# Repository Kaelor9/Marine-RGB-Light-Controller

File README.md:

<h1 align="center">Marine RGB Light Controller</h1>

<p align="center">
  Professional ESP32-S3 controller for addressable RGB LED installations in marine, automotive and industrial environments.
</p>

<p align="center">
  
</p>

---

## About

The **Marine RGB Light Controller** is a custom-designed ESP32-S3 controller developed for reliable operation in demanding electrical environments.

Unlike generic ESP32 development boards, it integrates protected power electronics, optically isolated inputs, dual level-shifted LED outputs and dedicated expansion interfaces into a single compact PCB.

Originally designed for marine lighting systems, the controller is equally suited for automotive, off-road, RV, architectural and industrial LED installations.

---

## Why this controller?

Most ESP32 development boards are intended for prototyping and require additional external circuitry before they are suitable for real-world installations.

The Marine RGB Light Controller integrates the essential hardware needed for reliable field deployment:

- Protected 12–24V power input
- Reverse polarity protection
- TVS surge suppression
- Optically isolated inputs
- Dual 5V LED data outputs
- USB-C programming
- GPIO & I²C expansion
- Compact installation-ready PCB

This significantly reduces external wiring while improving robustness and long-term reliability.

---

## Key Features

- ⚡ Protected 12–24V DC controller input
- 🔋 Direct VIN pass-through LED power output
- 🌈 Two independent 5V level-shifted LED data outputs
- 🔒 Two high-speed optically isolated digital inputs
- 📡 Wi-Fi & Bluetooth LE
- 🔌 USB-C programming
- 🔧 GPIO & I²C expansion
- 🛡 TVS, fuse and reverse polarity protection
- ⚓ Designed for harsh electrical environments

---

## Applications

The controller is suitable for a wide range of professional LED installations, including:

- ⚓ Marine lighting
- 🚙 Automotive lighting
- 🏕 Camper & RV installations
- 🏭 Industrial automation
- 🏡 Architectural lighting
- 💡 Custom RGB LED projects

---

## Hardware

The PCB integrates everything required for a professional LED controller:

- ESP32-S3-WROOM-1-N8R8
- High-efficiency buck converter
- Low-noise 3.3V LDO
- USB-C programming interface
- Dual 5V level shifters
- High-speed optocouplers
- Protected controller power supply
- GPIO & I²C expansion
- Dedicated LED power distribution

---

## Technical Specifications

| Feature | Specification |
|---------|---------------|
| MCU | ESP32-S3-WROOM-1-N8R8 |
| Flash | 8 MB |
| PSRAM | 8 MB |
| Input Voltage | 12–24V DC |
| Controller Protection | Fuse + Reverse Polarity + TVS |
| LED Supply | Direct VIN Pass-through |
| LED Outputs | 2 × 5V Logic (Level Shifted) |
| Digital Inputs | 2 × Optically Isolated |
| Wireless | Wi-Fi 2.4 GHz + Bluetooth LE |
| USB | USB-C |
| Expansion | GPIO + I²C |

---

## Pinout

| Connection | Function |
|------------|----------|
| VIN | 12–24V DC Input |
| AUX Power | Direct VIN Pass-through |
| DATA 1 | 5V LED Data Output |
| DATA 2 | 5V LED Data Output |
| ISO IN1 | Optically Isolated Input |
| ISO IN2 | Optically Isolated Input |
| SDA / SCL | I²C Expansion |
| IO8 / IO9 | GPIO Expansion |
| IO10 / IO11 | GPIO Expansion |
| 3V3 | 3.3V Output |
| 5V | 5V Output |
| GND | Ground |

---

## Gallery

---

## Software

The firmware is developed for the ESP32-S3 using the Arduino framework and is designed around a modern, responsive web interface.

Configuration is performed directly from any web browser without requiring additional software. The modular firmware architecture allows new LED effects and features to be added easily.

Current and planned features include:

- Modern Web UI
- RGB Color Picker
- Brightness Control
- LED Effects
- Wi-Fi Configuration
- mDNS Support
- OTA Firmware Updates
- FastLED Support
- Configuration Storage

---

## Repository Structure

```text
.
├── docs/
│   ├── images/
│   ├── hardware.md
│   ├── software.md
│   └── fabrication.md
│
├── firmware/
│   └── Marine_RGB_Controller/
│
├── hardware/
│   ├── kicad/
│   ├── fabrication/
│   └── 3d/
│
├── site/
│
├── LICENSE
└── README.md
```

---

## Documentation

Project documentation is located inside the **docs** directory.

Available documentation includes:

- Hardware Design
- Power Supply
- LED Outputs
- Optically Isolated Inputs
- Pinout
- Firmware
- Fabrication
- Getting Started

---

## Important Information

> [!IMPORTANT]
>
> The **LED power output is a direct pass-through of the input supply voltage.**
>
> - LED VOUT = VIN
> - The LED supply is **not reverse polarity protected**
> - The LED supply is **not fused**
> - Only the controller electronics are protected by the onboard fuse, TVS diode and reverse polarity protection
> - External protection should be added where required by the installation

---

## Project Status

| Hardware | Firmware | Documentation |
|----------|----------|---------------|
| ✅ Revision 1 Complete | 🚧 In Development | 🚧 In Progress |

---

## Roadmap

### Hardware

- [x] Hardware Revision 1
- [x] Protected Power Supply
- [x] USB-C Programming
- [x] Dual LED Outputs
- [x] Optically Isolated Inputs

### Firmware

- [ ] Complete Web Interface
- [ ] OTA Updates
- [ ] MQTT Support
- [ ] Home Assistant Integration
- [ ] Additional LED Effects
- [ ] Configuration Backup & Restore

---

## License

This project is proprietary.

Copyright © 2026 Anders Merrild

All rights reserved.

No permission is granted to copy, modify, distribute, manufacture, publish, sublicense or use any part of this project without prior written permission from the copyright holder.

See the [LICENSE](LICENSE) file for full terms.

---

<p align="center">

Designed and developed by <strong>Kaelor9</strong>

<br>

ESP32 • Marine Electronics • Professional RGB Lighting Controller

</p>

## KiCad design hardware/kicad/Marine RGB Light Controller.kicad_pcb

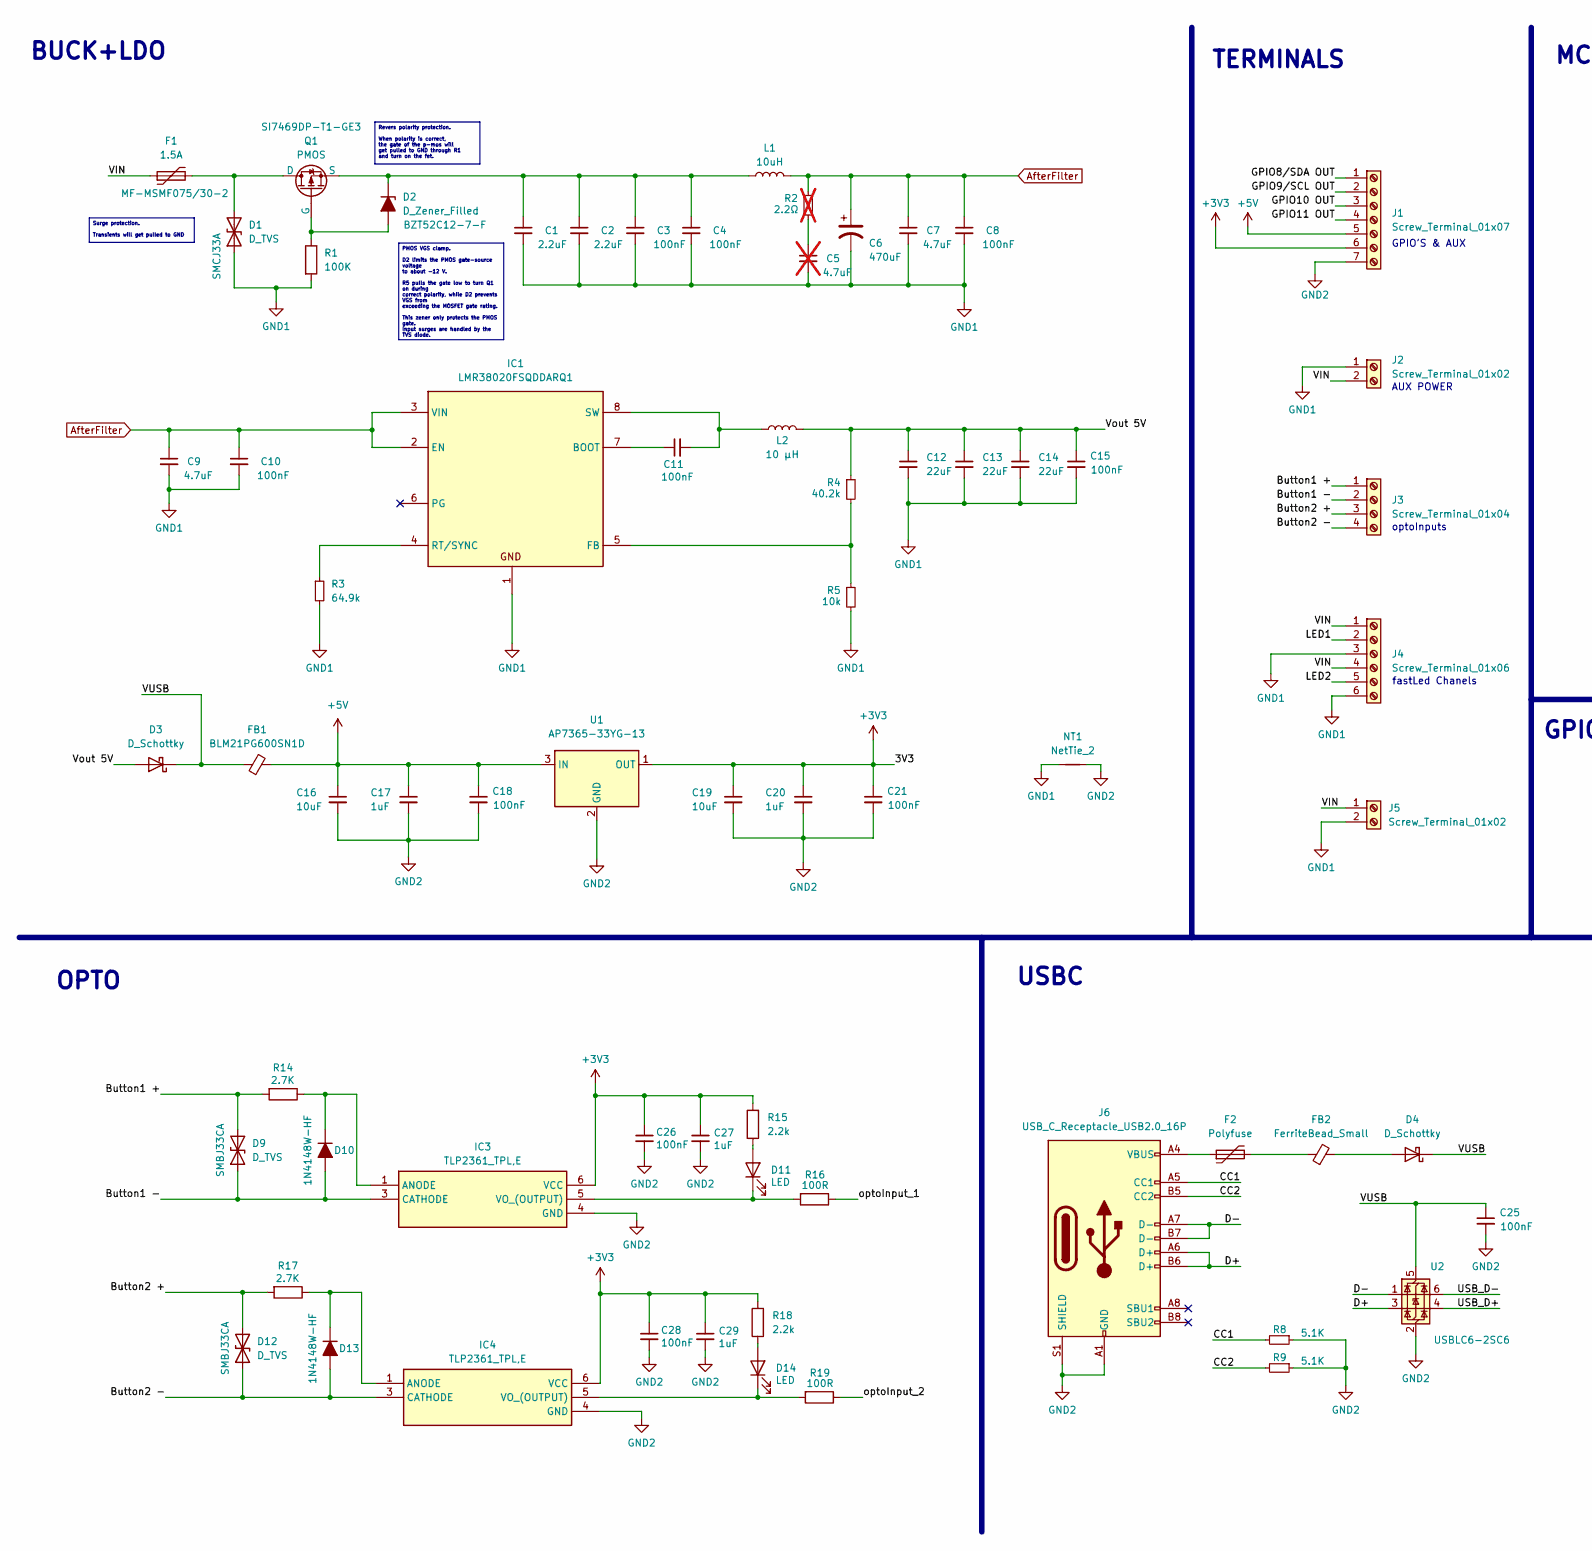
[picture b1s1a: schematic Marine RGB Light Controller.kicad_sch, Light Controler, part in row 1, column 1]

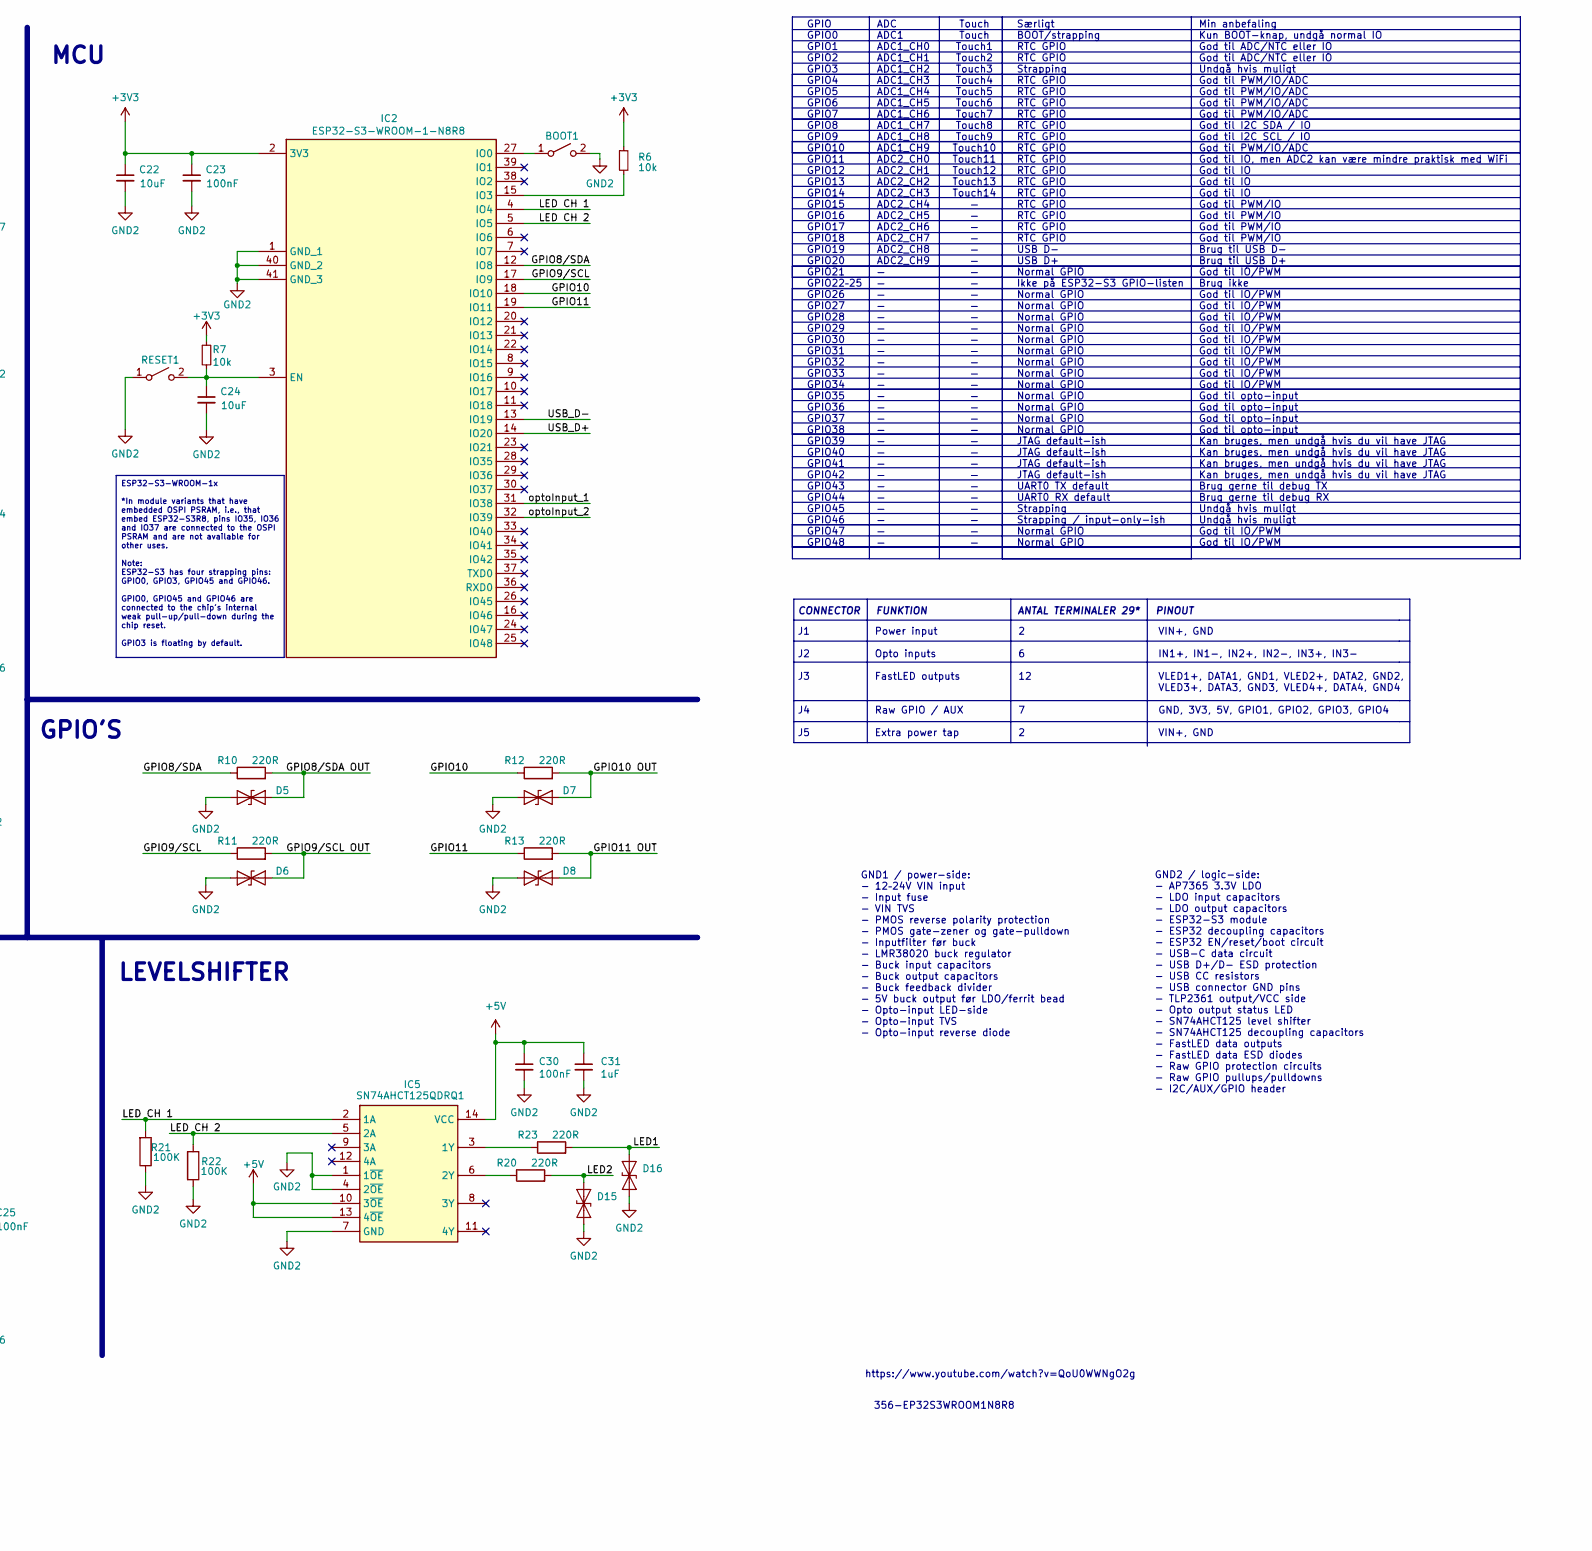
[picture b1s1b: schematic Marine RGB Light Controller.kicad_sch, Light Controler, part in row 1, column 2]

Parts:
BOOT1: SW [PTS810SJM250SMTRLFS]
C1, C2: 2.2uF; C_1206_3216Metric; Voltage Rating VDC 100V
C3, C4, C8, C10: 100nF; C_0603_1608Metric; Voltage Rating VDC 100V
C5: 4.7uF; C_1206_3216Metric; Voltage Rating VDC 100V; not fitted
C6: 470uF; CP_Radial_D12.5mm_P5.00mm; Voltage Rating VDC 63V
C7, C9: 4.7uF; C_1206_3216Metric; Voltage Rating VDC 100V
C11, C15, C18, C21, C23, C25, C26, C28, C30: 100nF; C_0603_1608Metric; Voltage Rating VDC 50V
C12, C13, C14: 22uF; C_1206_3216Metric; Voltage Rating VDC 16V
C16, C19: 10uF; C_1206_3216Metric; Voltage Rating VDC 16V
C17, C20: 1uF; C_0805_2012Metric; Voltage Rating VDC 25V
C22, C24: 10uF; C_0603_1608Metric; Voltage Rating VDC 35V
C27, C29, C31: 1uF; C_0805_2012Metric; Voltage Rating VDC 50V
D1: D_TVS; D_SMC
D2: D_Zener_Filled; D_SOD-123
D3, D4: D_Schottky; D_SOD-123
D5, D6, D7, D8, D15, D16: SD05_SOD323; D_SOD-323
D9, D12: D_TVS; D_SMB
D10, D13: D_SOD-123
D11, D14: LED; LED_0603_1608Metric
F1: 1.5A; Fuse_1812_4532Metric; Voltage Rating VDC 30 VDC
F2: Polyfuse; Fuse_1206_3216Metric
FB1: BLM21PG600SN1D; R_0805_2012Metric
FB2: FerriteBead_Small; R_0805_2012Metric
IC1: LMR38020FSQDDARQ1; Texas_R-PDSO-G8_EP2.95x4.9mm_Mask2.4x3.1mm; Voltage Rating VDC 80V
IC2: ESP32-S3-WROOM-1-N8R8; ESP32S3WROOM1N8R8; Mouser Part Number 356-EP32S3WROOM1N8R8
IC3, IC4: TLP2361_TPL,E; SOIC-6; Mouser Part Number 757-TLP2361(TPLE
IC5: SN74AHCT125QDRQ1; SOIC-14_3.9x8.7mm_P1.27mm; Mouser Part Number 595-SN74AHCT125QDRQ1
J1: Screw_Terminal_01x07; Fixed Terminal Blocks 7P 3.5mm 90DEG
J2: Screw_Terminal_01x02; Fixed Terminal Blocks 2P 3.5mm 0DEG
J3: Screw_Terminal_01x04; Fixed Terminal Blocks 4P 3.5mm 90DEG
J4: Screw_Terminal_01x06; Fixed Terminal Blocks 6P 3.5mm 90DEG
J5: Screw_Terminal_01x02; 2_Position Screw Terminal 5mm Pitch
J6: USB_C_Receptacle_USB2.0_16P; USB C [USB494000A]
L1: 10uH; L_Bourns_SRP1038C_10.0x10.0mm
L2: 10 µH; L_12x12mm_H6mm
NT1: NetTie_2; NetTie-2_SMD_Pad0.5mm
Q1: PMOS; P-MOS [SI7141DPT1GE3]; Voltage Rating VDC 80V
R1, R21, R22: 100K; R_0603_1608Metric
R2: 2.2Ω; R_1206_3216Metric; Voltage Rating VDC 200V; not fitted
R3: 64.9k; R_0603_1608Metric; Voltage Rating VDC 150 V
R4: 40.2k; R_0603_1608Metric; Voltage Rating VDC 150V
R5, R6, R7: 10k; R_0603_1608Metric
R8, R9: 5.1K; R_0603_1608Metric; Voltage Rating VDC 150V
R10, R11, R12, R13, R20, R23: 220R; R_0805_2012Metric; Voltage Rating VDC 150V
R14, R17: 2.7K; R_1206_3216Metric
R15, R18: 2.2k; R_0603_1608Metric
R16, R19: 100R; R_0603_1608Metric
RESET1: SW [PTS810SJM250SMTRLFS]
U1: AP7365-33YG-13; SOT-89-3
U2: USBLC6-2SC6; SOT-23-6

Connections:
+3V3: C19.1, C20.1, C21.1, C22.1, C23.1, C26.1, C27.1, C28.1, C29.1, IC2.2 (3V3), IC3.6 (VCC), IC4.6 (VCC), J1.6, R6.1, R7.1, R15.2, R18.2, U1.1 (OUT)
+5V: C16.1, C17.1, C18.1, C30.1, C31.1, FB1.2, IC5.10 (3~OE), IC5.13 (4~OE), IC5.14 (VCC), J1.5, U1.3 (IN)
/Button1 +: D9.2 (A2), J3.1, R14.2
/Button1 -: D9.1 (A1), D10.2 (A), IC3.3 (CATHODE), J3.2
/Button2 +: D12.2 (A2), J3.3, R17.2
/Button2 -: D12.1 (A1), D13.2 (A), IC4.3 (CATHODE), J3.4
/CC1: J6.A5 (CC1), R8.2
/CC2: J6.B5 (CC2), R9.2
/D+: J6.A6 (D+), J6.B6 (D+), U2.3 (I/O2)
/D-: J6.A7 (D-), J6.B7 (D-), U2.1 (I/O1)
/GPIO8/SDA: IC2.12 (IO8), R10.1
/GPIO8/SDA OUT: D5.2 (A2), J1.1, R10.2
/GPIO9/SCL: IC2.17 (IO9), R11.1
/GPIO9/SCL OUT: D6.2 (A2), J1.2, R11.2
/GPIO10: IC2.18 (IO10), R12.1
/GPIO10 OUT: D7.2 (A2), J1.3, R12.2
/GPIO11: IC2.19 (IO11), R13.1
/GPIO11 OUT: D8.2 (A2), J1.4, R13.2
/LED1: D16.2 (A2), J4.2, R23.2
/LED2: D15.2 (A2), J4.5, R20.2
/LED CH 1: IC2.4 (IO4), IC5.2 (1A), R21.2
/LED CH 2: IC2.5 (IO5), IC5.5 (2A), R22.2
/USB_D+: IC2.14 (IO20), U2.4 (I/O2)
/USB_D-: IC2.13 (IO19), U2.6 (I/O1)
/VIN: F1.1, J2.2, J4.1, J4.4, J5.1
/VUSB: C25.1, D3.1 (K), D4.1 (K), FB1.1, U2.5 (VBUS)
/Vout 5V: C12.1, C13.1, C14.1, C15.1, D3.2 (A), L2.2, R4.1
/optoInput_1: IC2.31 (IO38), R16.1
/optoInput_2: IC2.32 (IO39), R19.1
AfterFilter: C6.1, C7.1, C8.1, C9.1, C10.1, IC1.2 (EN), IC1.3 (VIN), L1.2, R2.1
GND1: C1.2, C2.2, C3.2, C4.2, C5.2, C6.2, C7.2, C8.2, C9.2, C10.2, C12.2, C13.2, C14.2, C15.2, D1.1 (A1), IC1.1, IC1.9 (EP), J2.1, J4.3, J4.6, J5.2, NT1.1, R1.2, R3.2, R5.2; also elsewhere on the board
GND2: BOOT1.2 (B), C16.2, C17.2, C18.2, C19.2, C20.2, C21.2, C22.2, C23.2, C24.2, C25.2, C26.2, C27.2, C28.2, C29.2, C30.2, C31.2, D5.1 (A1), D6.1 (A1), D7.1 (A1), D8.1 (A1), D15.1 (A1), D16.1 (A1), IC2.1 (GND_1), IC2.40 (GND_2), IC2.41 (GND_3), IC2.42 (GND_4), IC2.43 (GND_5), IC2.44 (GND_6), IC2.45 (GND_7), IC2.46 (GND_8), IC2.47 (GND_9), IC2.48 (GND_10), IC2.49 (GND_11), IC3.4 (GND), IC4.4 (GND), IC5.1 (1~OE), IC5.4 (2~OE), IC5.7 (GND), J1.7, J6.A1 (GND), J6.A12 (GND), J6.B1 (GND), J6.B12 (GND), J6.S1 (SHIELD), NT1.2, R8.1, R9.1, R21.1, R22.1, RESET1.1 (A), U1.2 (GND), U2.2 (GND); also elsewhere on the board
unnamed 32: BOOT1.1 (A), IC2.27 (IO0); also elsewhere on the board
unnamed: C5.1, R2.2
unnamed: D1.2 (A2), F1.2, Q1.3 (D)
unnamed: D2.2 (A), Q1.2 (G), R1.1
unnamed: C1.1, C2.1, C3.1, C4.1, D2.1 (K), L1.1, Q1.1 (S)
unnamed: D4.2 (A), FB2.2
unnamed: D10.1 (K), IC3.1 (ANODE), R14.1
unnamed: D11.2 (A), R15.1
unnamed: D11.1 (K), IC3.5 (VO_(OUTPUT)), R16.2
unnamed: D13.1 (K), IC4.1 (ANODE), R17.1
unnamed: D14.2 (A), R18.1
unnamed: D14.1 (K), IC4.5 (VO_(OUTPUT)), R19.2
unnamed: F2.1, J6.A4 (VBUS), J6.A9 (VBUS), J6.B4 (VBUS), J6.B9 (VBUS)
unnamed: F2.2, FB2.1
unnamed: C11.1, IC1.7 (BOOT)
unnamed: IC1.5 (FB), R4.2, R5.1
unnamed: IC1.4 (RT/SYNC), R3.1
unnamed: C11.2, IC1.8 (SW), L2.1
unnamed 50: C24.1, IC2.3 (EN), R7.2, RESET1.2 (B); also elsewhere on the board
unnamed: IC2.15 (IO3), R6.2
unnamed: IC5.3 (1Y), R23.1
unnamed: IC5.6 (2Y), R20.1

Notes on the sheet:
ESP32-S3-WROOM-1x *In module variants that have embedded OSPI PSRAM, i.e., that embed ESP32-S3R8, pins IO35, IO36 and IO37 are connected to the OSPI PSRAM and are not available for other uses. Note: ESP32-S3 has four strapping pins: GPIO0, GPIO3, GPIO45 and GPIO46. GPIO0, GPIO45 and GPIO46 are conn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
PMOS VGS clamp. D2 limits the PMOS gate-source voltage to about -12 V. R5 pulls the gate low to turn Q1 on during correct polarity, while D2 prevents VGS from exceeding the MOSFET gate rating. This zener only protects the PMOS gate. Input surges are handled by the TVS diode.
Surge protection. Transients will get pulled to GND
Revers polarity protection. When polarity is correct, the gate of the p-mos will get pulled to GND through R1 and turn on the fet.
VIN+, GND IN1+, IN1-, IN2+, IN2-, IN3+, IN3- VLED1+, DATA1, GND1, VLED2+, DATA2, GND2, VLED3+, DATA3, GND3, VLED4+, DATA4, GND4 GND, 3V3, 5V, GPIO1, GPIO2, GPIO3, GPIO4 VIN+, GND
GND1 / power-side: - 12–24V VIN input - Input fuse - VIN TVS - PMOS reverse polarity protection - PMOS gate-zener og gate-pulldown - Inputfilter før buck - LMR38020 buck regulator - Buck input capacitors - Buck output capacitors - Buck feedback divider - 5V buck output før LDO/ferrit bead - Opto-in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
USBC
GPIO'S & AUX
CONNECTOR FUNKTION ANTAL TERMINALER 29* PINOUT
optoInputs
AUX POWER
2 6 12 7 2
Min anbefaling Kun BOOT-knap, undgå normal IO God til ADC/NTC eller IO God til ADC/NTC eller IO Undgå hvis muligt God til PWM/IO/ADC God til PWM/IO/ADC God til PWM/IO/ADC God til PWM/IO/ADC God til I2C SDA / IO God til I2C SCL / IO God til PWM/IO/ADC God til IO, men ADC2 kan være mindre praktisk me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
Touch Touch Touch1 Touch2 Touch3 Touch4 Touch5 Touch6 Touch7 Touch8 Touch9 Touch10 Touch11 Touch12 Touch13 Touch14 — — — — — — — — — — — — — — — — — — — — — — — — — — — — — — —
https://www.youtube.com/watch?v=QoU0WWNgO2g
OPTO
Power input Opto inputs FastLED outputs Raw GPIO / AUX Extra power tap
fastLed Chanels
Særligt BOOT/strapping RTC GPIO RTC GPIO Strapping RTC GPIO RTC GPIO RTC GPIO RTC GPIO RTC GPIO RTC GPIO RTC GPIO RTC GPIO RTC GPIO RTC GPIO RTC GPIO RTC GPIO RTC GPIO RTC GPIO RTC GPIO USB D- USB D+ Normal GPIO Ikke på ESP32-S3 GPIO-listen Normal GPIO Normal GPIO Normal GPIO Normal GPIO Normal GPI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
ADC ADC1 ADC1_CH0 ADC1_CH1 ADC1_CH2 ADC1_CH3 ADC1_CH4 ADC1_CH5 ADC1_CH6 ADC1_CH7 ADC1_CH8 ADC1_CH9 ADC2_CH0 ADC2_CH1 ADC2_CH2 ADC2_CH3 ADC2_CH4 ADC2_CH5 ADC2_CH6 ADC2_CH7 ADC2_CH8 ADC2_CH9 — — — — — — — — — — — — — — — — — — — — — — — — —
GND2 / logic-side: - AP7365 3.3V LDO - LDO input capacitors - LDO output capacitors - ESP32-S3 module - ESP32 decoupling capacitors - ESP32 EN/reset/boot circuit - USB-C data circuit - USB D+/D- ESD protection - USB CC resistors - USB connector GND pins - TLP2361 output/VCC side - Opto output statu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
TERMINALS
356-EP32S3WROOM1N8R8
BUCK+LDO
GPIO GPIO0 GPIO1 GPIO2 GPIO3 GPIO4 GPIO5 GPIO6 GPIO7 GPIO8 GPIO9 GPIO10 GPIO11 GPIO12 GPIO13 GPIO14 GPIO15 GPIO16 GPIO17 GPIO18 GPIO19 GPIO20 GPIO21 GPIO22–25 GPIO26 GPIO27 GPIO28 GPIO29 GPIO30 GPIO31 GPIO32 GPIO33 GPIO34 GPIO35 GPIO36 GPIO37 GPIO38 GPIO39 GPIO40 GPIO41 GPIO42 GPIO43 GPIO44 GPIO45 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
J1 J2 J3 J4 J5
LEVELSHIFTER
GPIO'S
MCU

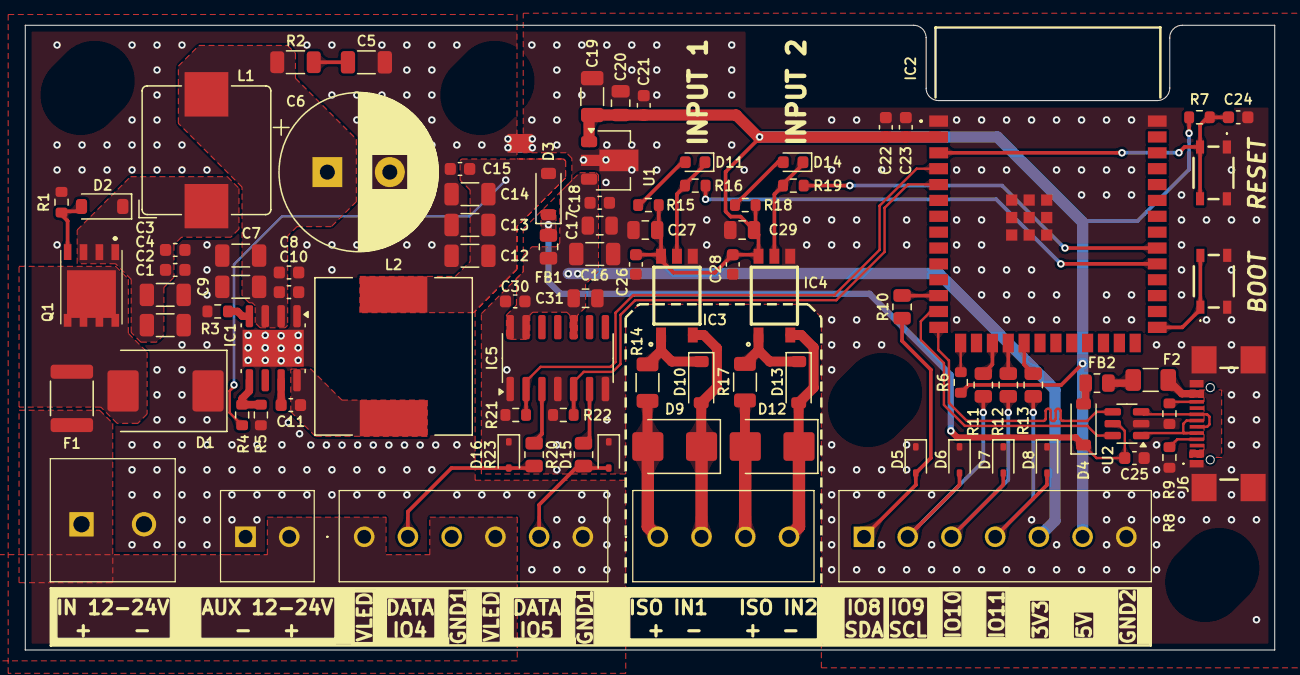
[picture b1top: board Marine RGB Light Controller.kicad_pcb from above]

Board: 2 copper layers, 100.0 x 50.0 mm, 94 parts (1 on the bottom side), 54 nets.

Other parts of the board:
BOOT: SW [PTS810SJM250SMTRLFS]
NT1#2: NetTie_2; NetTie-2_SMD_Pad0.5mm
RESET: SW [PTS810SJM250SMTRLFS]

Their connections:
GND1: NT1#2.1; also elsewhere on the board
GND2: BOOT.2 (B), NT1#2.2, RESET.1 (A); also elsewhere on the board
unnamed 32: BOOT.1 (A); also elsewhere on the board
unnamed 50: RESET.2 (B); also elsewhere on the board

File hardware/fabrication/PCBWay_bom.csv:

Designator,Quantity,Value,Footprint,Package,MPN,DNP,Mount_Type,Description,Mfr.,Mfr. No:,Voltage Rating VDC,URL,Height,Mouser Part Number,Mouser Price/Stock,Manufacturer_Name,Mfr:
,1,,,,,,tht,,,,,,,,,,
"BOOT, RESET",2,~,SW [PTS810SJM250SMTRLFS],,,,smt,Single Pole Single Throw (SPST) switch,PTS810SJM250SMTR LFS,C&K,,,,,,,
"C1, C2",2,2.2uF,C_1206_3216Metric,,,,smt,"Unpolarized capacitor, small symbol",Wurth Elektronik,885012208124,100V,,,,,,
"C10, C11, C15, C18, C21, C23, C25, C26, C28, C3, C30, C4, C8",13,100nF,C_0603_1608Metric,,,,smt,"[C4,C8]Unpolarized capacitor, small symbol; [C30]Multilayer Ceramic Capacitors MLCC - SMD/SMT 0603 MLCC X7R 0.1 uF, +/- 10% 50 V T&R MG","[C4,C8]Murata Electronics; [C30]Walsin","[C4,C8]GRM188R72A104KA35D; [C30]MG18B104K500CT","[C4,C8]100V; [C30]50V",,,,,,
"C12, C13, C14",3,22uF,C_1206_3216Metric,,,,smt,Multilayer Ceramic Capacitors MLCC - SMD/SMT PLEASE SEE SUGGESTED ALTERNATE MSASE105SC6105MFNA01,TAIYO YUDEN,EMK316BB7226ML-T,16V,,,,,,
"C16, C19",2,10uF,C_1206_3216Metric,,,,smt,Multilayer Ceramic Capacitors MLCC - SMD/SMT CGA 1206 16V 10uF X7R 10% AEC-Q200,TDK,CGA5L1X7R1C106K160AC,16V,,,,,,
"C17, C20, C27, C29, C31",5,1uF,C_0805_2012Metric,,,,smt,"[C17,C20]Unpolarized capacitor, small symbol; [C27,C29]Multilayer Ceramic Capacitors MLCC - SMD/SMT KAM21KR71H105KL NEW GLOBAL PN 50V 1uF X7 A 581-KAM21KR71H105KL; [C31]Multilayer Ceramic Capacitors MLCC - SMD/SMT Automotive MLCC 1uF, 10%, X7R, 50VDC","[C17,C20]Samsung Electro-Mechanics; [C27,C29,C31]KYOCERA AVX","[C17,C20]CL21B105KAFNFNE; [C27,C29]08055C105K4T4A; [C31]KAM21KR71H105KL","[C17,C20]25V; [C27,C29,C31]50V",,,,,,
"C22, C24",2,10uF,C_0603_1608Metric,,,,smt,Multilayer Ceramic Capacitors MLCC - SMD/SMT 10 uF 35 VDC 20% 0603 X5R,Murata Electronics,GRM188R6YA106MA73D,35V,,,,,,
C5,1,4.7uF,C_1206_3216Metric,,,Yes,smt,"Unpolarized capacitor, small symbol",TDK,CGA5L1X7R2A475K160AC,100V,,,,,,
C6,1,470uF,CP_Radial_D12.5mm_P5.00mm,,,,tht,Aluminium Electrolytic Capacitors - Radial Leaded 470uF 63V 20% 12.5 x 25,Vishay,MAL217058471E3,63V,https://www.mouser.dk/ProductDetail/Vishay -BC-Components/MAL217058471E3?qs=sGAEpiMZZ MvwFf0viD3Y3a3yb5D6sPUge%2FhbHmEvBGTt46%2F Okru66g%3D%3D,,,,,
"C7, C9",2,4.7uF,C_1206_3216Metric,,,,smt,"Unpolarized capacitor, small symbol",TDK,CGA5L1X7R2A475K160AC,100V,,,,,,
D1,1,D_TVS,D_SMC,,,,smt,ESD Protection Diodes / TVS Diodes 33volts 5uA 28.1 Amps Uni-Dir,Bourns,SMCJ33A,,,,,,,
"D10, D13",2,~,D_SOD-123,,,,smt,Small Signal Switching Diodes DIODE SWITCHING 100V 150mA 500mW SOD-123,Comchip Technology,1N4148W-HF,,,,,,,
"D11, D14",2,LED,LED_0603_1608Metric,,,,smt,Single Colour LEDs GREEN WATER CLEAR,Kingbright,APT1608SGC,,,,,,,
"D12, D9",2,D_TVS,D_SMB,,,,smt,ESD Protection Diodes / TVS Diodes 600W 33V 5% Bi-Directional,Littelfuse,SMBJ33CA,,,,,,,
"D15, D16, D5, D6, D7, D8",6,SD05_SOD323,D_SOD-323,,,,smt,ESD Protection Diodes / TVS Diodes 5V 450W 30A BiDirectional,Littelfuse,SD05C-01FTG,,,,,,,
D2,1,D_Zener_Filled,D_SOD-123,,,,smt,"Zener diode, filled shape",Diodes Incorporated,BZT52C12-7-F,,,,,,,
"D3, D4",2,D_Schottky,D_SOD-123,,,,smt,Schottky Diodes & Rectifiers RECT 40V 1A SM SCHOTTKY,Nexperia,PMEG40T10ERX,,,,,,,
F1,1,1.5A,Fuse_1812_4532Metric,,,,smt,Resettable Fuses - PPTC PTC RESETTABLE 0.75A 30V SMD 1812,Bourns,MF-MSMF075/30-2,30 VDC,https://www.mouser.dk/ProductDetail/Bourns/MF-MSMF075-30-2?q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,,,,,
F2,1,Polyfuse,Fuse_1206_3216Metric,,,,smt,Resettable Fuses - PPTC 1206 Resettable SMD PPTC 0.50A/16V,Bourns,MF-NSMF050/16X-2,,,,,,,
FB1,1,BLM21PG600SN1D,R_0805_2012Metric,,,,smt,Ferrite Beads 60 OHM 25% Alternate Sizing Guide Below,Murata Electronics,BLM21PG600SN1D,,,,,,,
FB2,1,FerriteBead_Small,R_0805_2012Metric,,,,smt,Ferrite Beads 22 OHM 25% Alternate Sizing Guide Below,Murata Electronics,BLM21PG220SN1D,,,,,,,
IC1,1,C,Texas_R-PDSO-G8_EP2.95x4.9mm_Mask2.4x3.1mm,,,,smt,"Switching Voltage Regulators Automotive SIMPLE SWITCHER power converter 4.2-V to 80-V, 2-A, synchronous buck converter",Texas Instruments,LMR38020FSQDDARQ1,80V,,,,,,
IC2,1,ESP32-S3-WROOM-1-N8R8,ESP32S3WROOM1N8R8,,ESP32-S3-WROOM-1-N8R8,,smt,"WiFi Modules - 802.11 (Engineering Samples Only) SMD Module, ESP32-S3R8 with 8 MB Octal PSRAM Die, 8 MB Quad SPI flash, PCB Antenna",,,,,3.25,356-EP32S3WROOM1N8R8,https://www.mouser.co.uk/ProductDetail/Espressif-Systems/ESP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,Espressif Systems,
"IC3, IC4",2,"TLP2361_TPL,E",SOIC-6,,"TLP2361(TPL,E",,smt,High Speed Optocouplers X36 PB Photocoupler Lo I/P cur 125 degC,,,,,,757-TLP2361(TPLE,https://www.mouser.co.uk/ProductDetail/Toshiba/TLP2361TPLE?q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,Toshiba,
IC5,1,SN74AHCT125QDRQ1,SOIC-14_3.9x8.7mm_P1.27mm,,SN74AHCT125QDRQ1,,smt,Automotive Catalog Quadruple Bus Buffer Gates With 3-State Outputs,,,,,1.75,595-SN74AHCT125QDRQ1,https://www.mouser.co.uk/ProductDetail/Texas-Instruments/SN7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,Texas Instruments,
J1,1,Screw_Terminal_01x07,Fixed Terminal Blocks 7P 3.5mm 90DEG,,,,tht,"Generic screw terminal, single row, 01x07, script generated (kicad-library-utils/schlib/autogen/connector/)",,,,,,,,,
J2,1,Screw_Terminal_01x02,Fixed Terminal Blocks 2P 3.5mm 0DEG,,,,tht,"Generic screw terminal, single row, 01x02, script generated (kicad-library-utils/schlib/autogen/connector/)",,,,,,,,,
J3,1,Screw_Terminal_01x04,Fixed Terminal Blocks 4P 3.5mm 90DEG,,,,tht,"Generic screw terminal, single row, 01x04, script generated (kicad-library-utils/schlib/autogen/connector/)",,,,,,,,,
J4,1,Screw_Terminal_01x06,Fixed Terminal Blocks 6P 3.5mm 90DEG,,,,tht,"Generic screw terminal, single row, 01x06, script generated (kicad-library-utils/schlib/autogen/connector/)",,,,,,,,,
J5,1,Screw_Terminal_01x02,2_Position Screw Terminal 5mm Pitch,,,,tht,"Generic screw terminal, single row, 01x02, script generated (kicad-library-utils/schlib/autogen/connector/)",,,,,,,,,
J6,1,USB_C_Receptacle_USB2.0_16P,USB C [USB494000A],,,,tht,"USB Connectors USB Type C, 2.0, 16P, Receptacle, Horizontal, Top Mount, SMT,T&R",GCT,USB4940-00-A,,,,,,,
L1,1,10uH,L_Bourns_SRP1038C_10.0x10.0mm,,,,smt,Power Inductors - SMD 10uH 20% SMD 1038 AEC-Q200,Bourns,SRP1038A-100M,,,,,,,
L2,1,10 µH,L_12x12mm_H6mm,,,,smt,FIXED IND 10UH 5.8A 20 MOHM SMD,,7447706100,,,,,,,Würth Elektronik
Q1,1,PMOS,P-MOS [SI7141DPT1GE3],,,,smt,MOSFETs,Vishay Semiconductors,SI7469DP-T1-GE3,80V,,,,,,
"R1, R21, R22",3,100K,R_0603_1608Metric,,,,smt,Resistor,YAGEO ,RC0603FR-07100KL ,,,,,,,
"R10, R11, R12, R13, R20, R23",6,220R,R_0805_2012Metric,,,,smt,Thick Film Resistors 1/4watts 220ohms 5%,KOA Speer,RK73B2ATTD221J,150V,,,,,,
"R14, R17",2,2.7K,R_1206_3216Metric,,,,smt,Thick Film Resistors CRGH1206 1% 2K7 0.5W,TE Connectivity / Holsworthy,CRGH1206F2K7,,,,,,,
"R15, R18",2,2.2k,R_0603_1608Metric,,,,smt,Thick Film Resistors 0603 Anti-sulfurated anti-surge resistor,Panasonic,ERJ-UP3J222V,,,,,,,
"R16, R19",2,100R,R_0603_1608Metric,,,,smt,,,,,,,,,,
R2,1,2.2Ω,R_1206_3216Metric,,,Yes,smt,Thick Film Resistors - SMD 2.2ohms 1% 100ppm,Vishay / Dale,RCC12062R20FKEA,200V,,,,,,
R3,1,64.9k,R_0603_1608Metric,,,,smt,Thick Film Resistors 0603 64.9Kohm 1% Anti-Surge AEC-Q200,Panasonic,ERJ-PA3F6492V,150 V,,,,,,
R4,1,40.2k,R_0603_1608Metric,,,,smt,"Resistor, small symbol",Panasonic,ERJ-UP3F4022V,150V,,,,,,
"R5, R6, R7",3,10k,R_0603_1608Metric,,,,smt,"Resistor, small symbol",YAGEO,RC0603FR-07100KL,,,,,,,
"R8, R9",2,5.1K,R_0603_1608Metric,,,,smt,Thick Film Resistors 0603 Anti-sulfurated anti-surge resistor,Panasonic,ERJ-UP3J512V,150V,,,,,,
U1,1,AP7365-33YG-13,SOT-89-3,,,,smt,"3.3V, 1.5A, Low Noise, Fast Transient Response LDO Regulator, SOT-223",,,,,,,,,
U2,1,USBLC6-2SC6,SOT-23-6,,,,smt,ESD Protection Diodes / TVS Diodes ESD Protection Low Cap,STMicroelectronics,USBLC6-2SC6,,,,,,,

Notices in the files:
README.md:
src="https://img.shields.io/badge/License-Proprietary-red"
